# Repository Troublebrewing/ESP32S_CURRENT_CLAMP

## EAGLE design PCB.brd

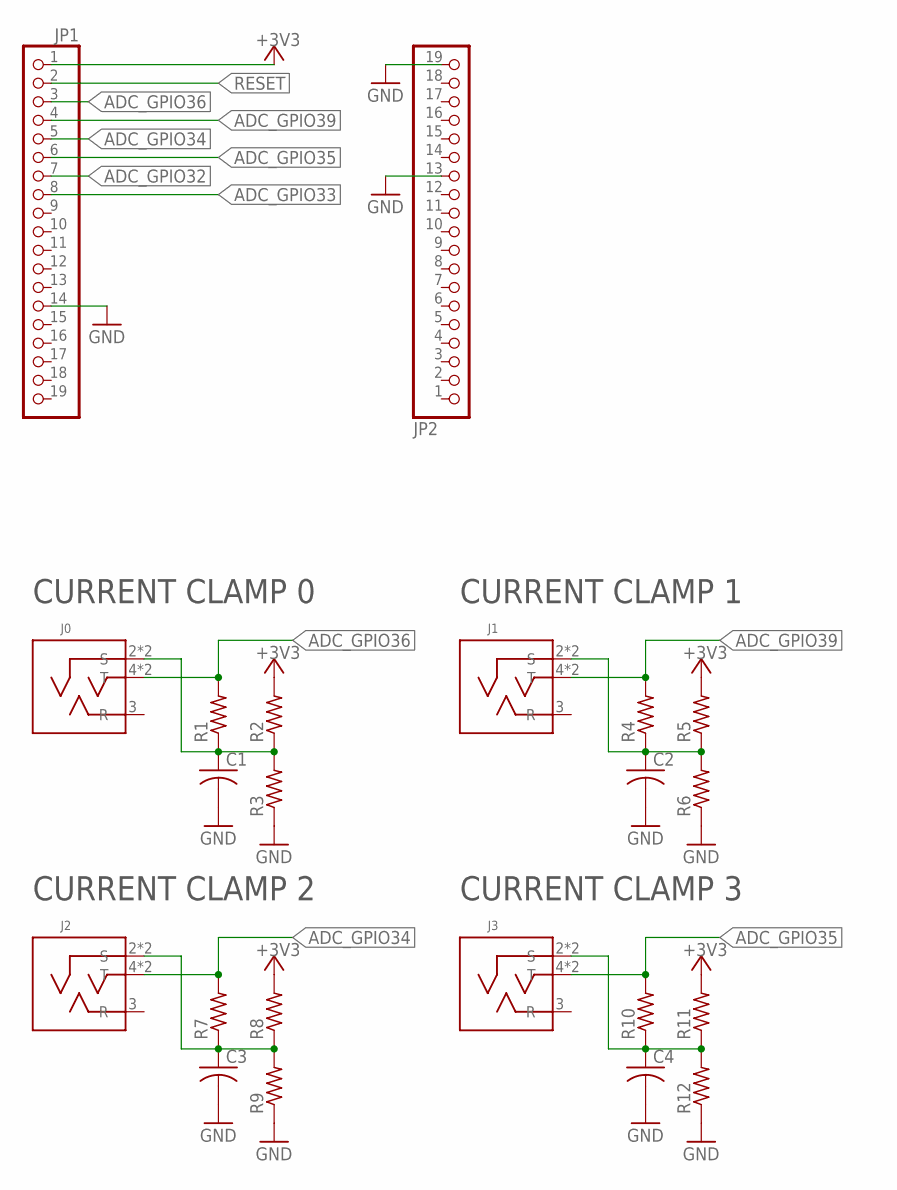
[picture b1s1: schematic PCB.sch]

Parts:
C1, C2, C3, C4: C-USC1206; C1206
J0, J1, J2, J3: BOOMELE_C18167; PJ-313
JP1, JP2: PINHD-1X19; 1X19
R1, R2, R3, R4, R5, R6, R7, R8, R9, R10, R11, R12: R-US_R1206; R1206

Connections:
+3V3: JP1.1, R2.2, R5.2, R8.2, R11.2
ADC_GPIO32: JP1.7
ADC_GPIO33: JP1.8
ADC_GPIO34: J2.4 (T), J2.4. (T), JP1.5, R7.2
ADC_GPIO35: J3.4 (T), J3.4. (T), JP1.6, R10.2
ADC_GPIO36: J0.4 (T), J0.4. (T), JP1.3, R1.2
ADC_GPIO39: J1.4 (T), J1.4. (T), JP1.4, R4.2
GND: C1.2, C2.2, C3.2, C4.2, JP1.14, JP2.13, JP2.19, R3.1, R6.1, R9.1, R12.1
unnamed: C2.1, J1.2 (S), J1.2. (S), R4.1, R5.1, R6.2
unnamed: C1.1, J0.2 (S), J0.2. (S), R1.1, R2.1, R3.2
unnamed: C3.1, J2.2 (S), J2.2. (S), R7.1, R8.1, R9.2
unnamed: C4.1, J3.2 (S), J3.2. (S), R10.1, R11.1, R12.2
RESET: JP1.2

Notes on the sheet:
CURRENT CLAMP 0
CURRENT CLAMP 1
CURRENT CLAMP 2
CURRENT CLAMP 3

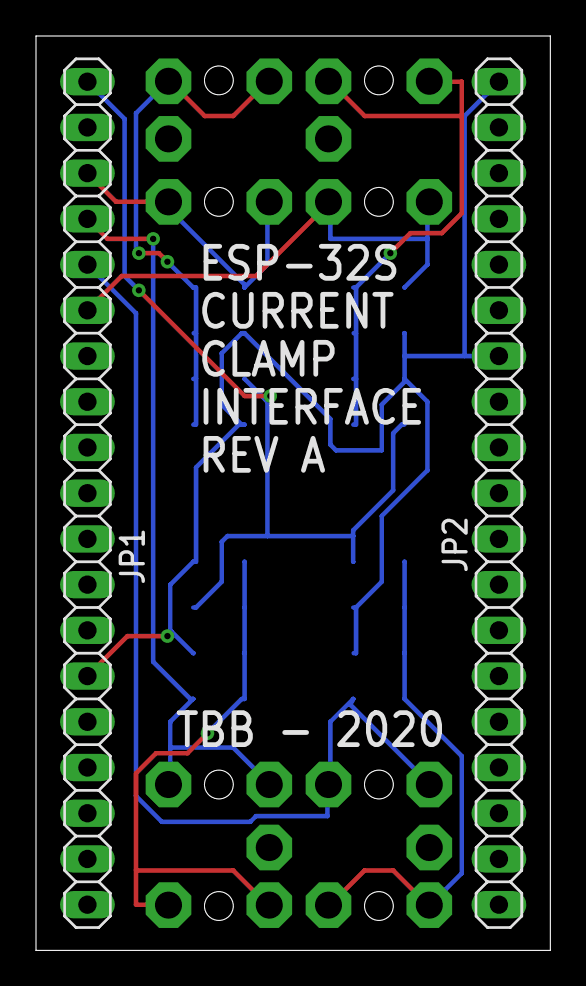
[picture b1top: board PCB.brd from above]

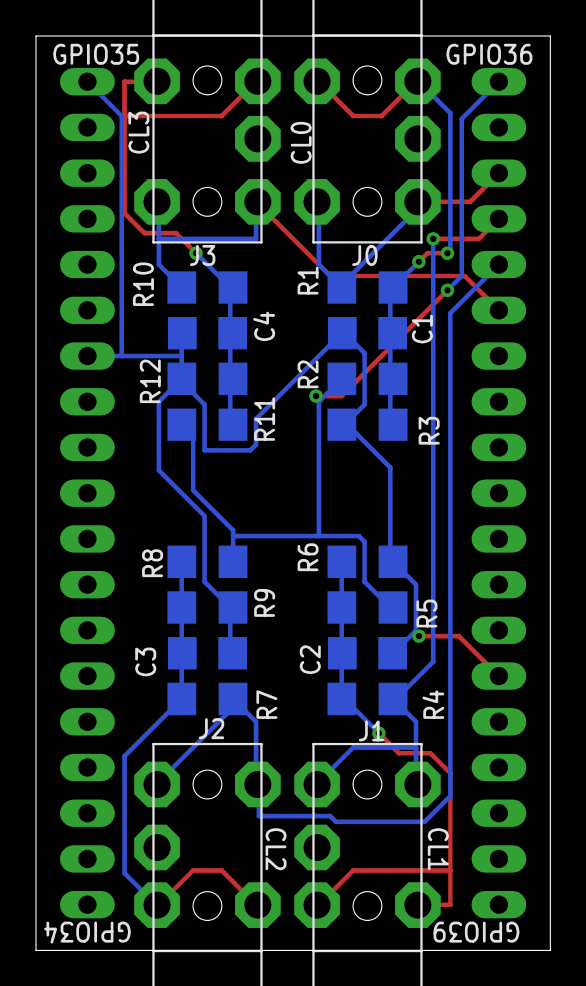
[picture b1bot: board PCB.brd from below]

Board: 2 copper layers, 28.6 x 50.8 mm, 22 parts (20 on the bottom side), 10 nets.

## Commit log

2020-02-26 Layed out schematic, pcb outline, and custom footprints. just need to route and drc now
2020-02-27 Revision A. Only 4 jacks can be nested between pins of ESP32 so design changed to accept only 4.
2020-02-27 fixed a couple silkscreen issues. regenerated gerber package
